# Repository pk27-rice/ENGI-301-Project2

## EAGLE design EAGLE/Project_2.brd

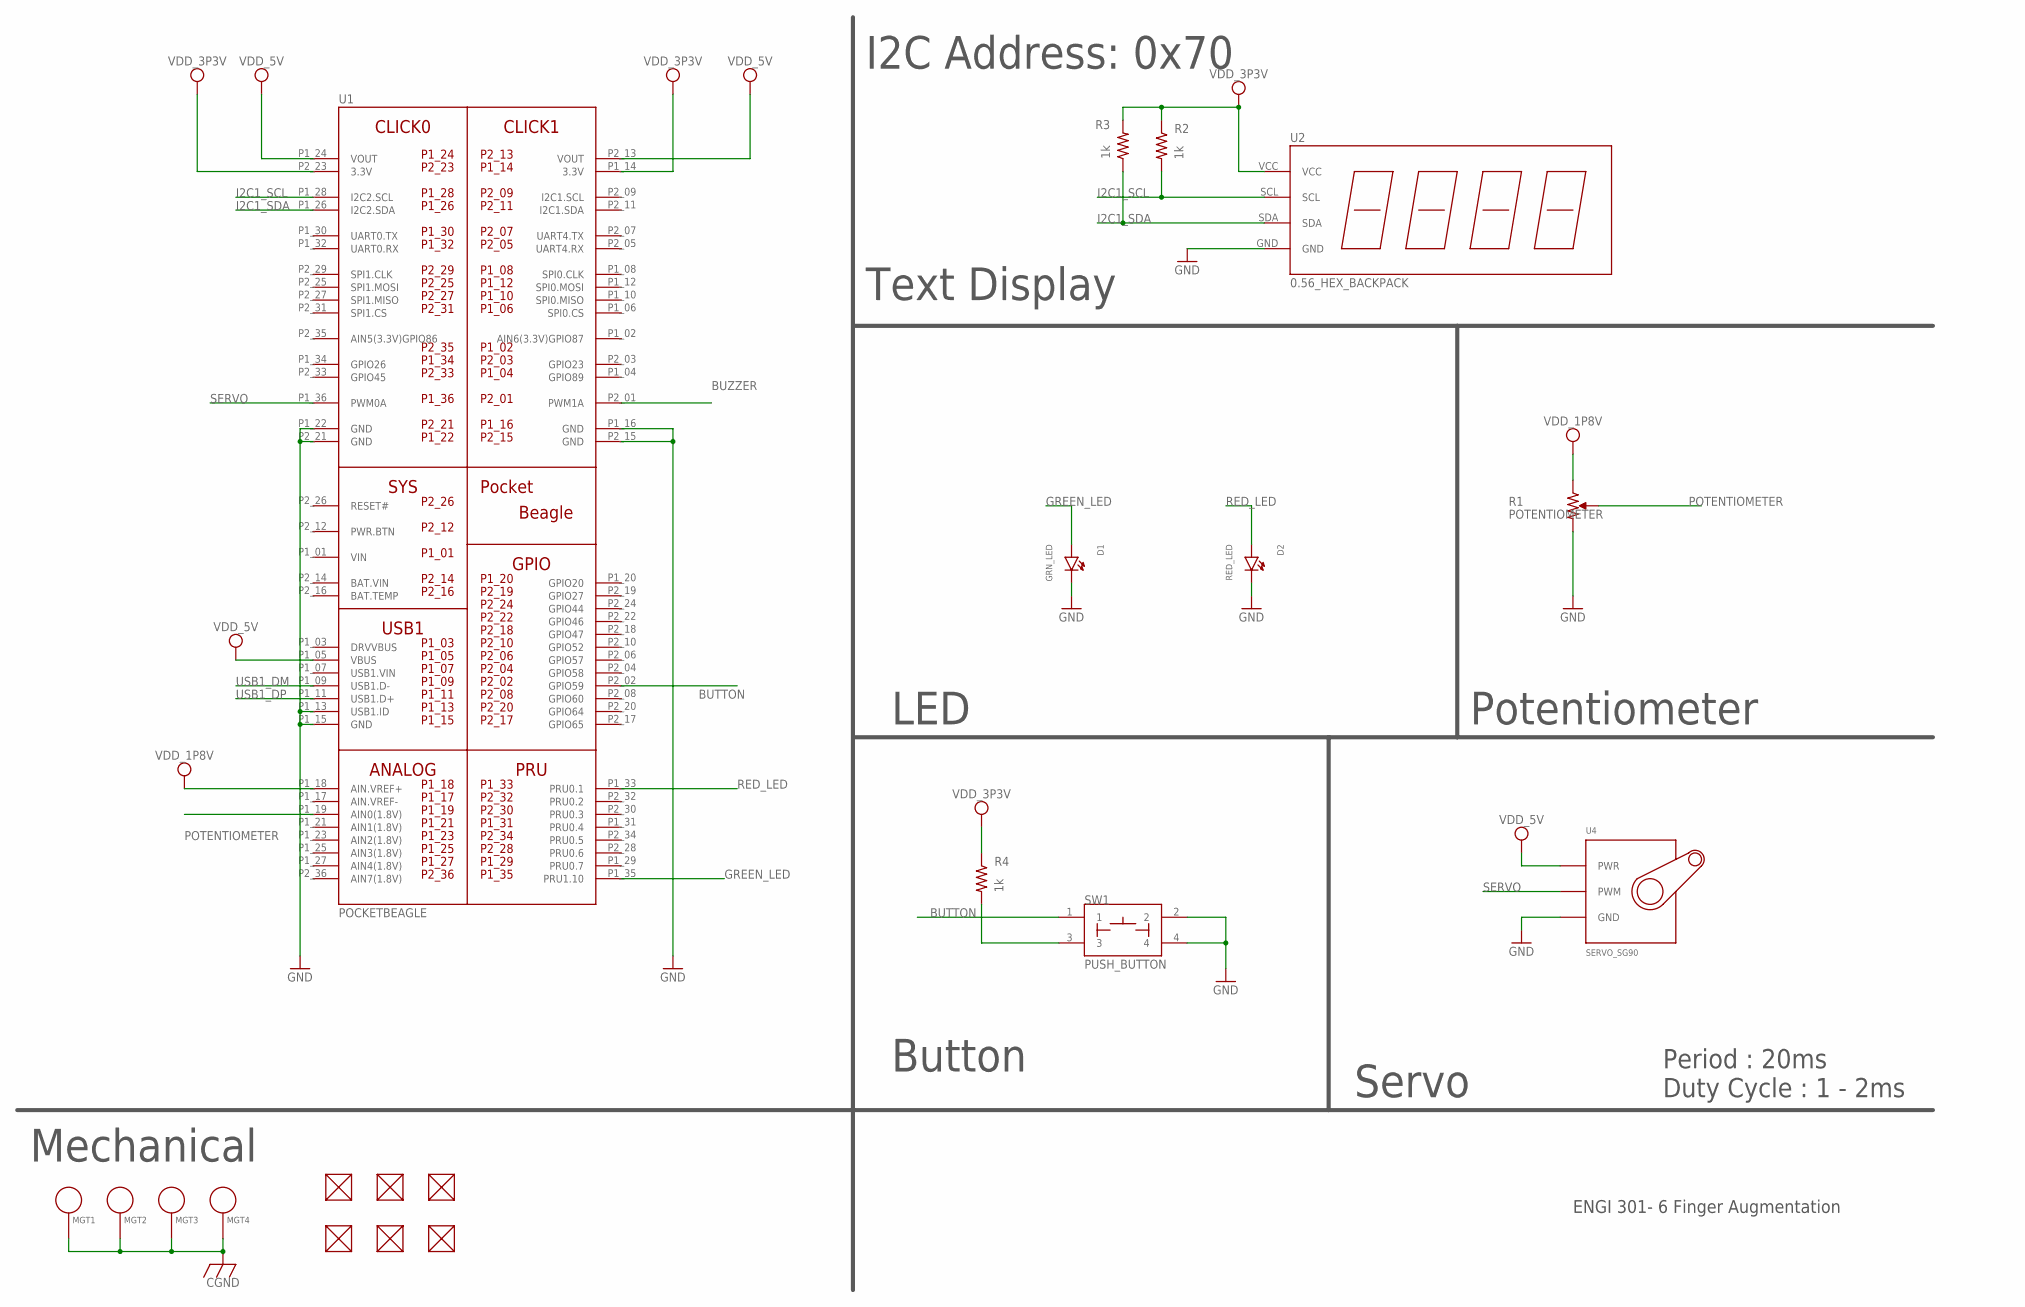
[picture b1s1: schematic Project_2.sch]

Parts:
D1: GRN_LED; EIA-STD
D2: RED_LED; EIA-STD
FUD1, FUD2, FUD3, FUD4, FUD5, FUD6: FIDUCIAL; FIDUCIAL_40MIL
MGT1, MGT2, MGT3, MGT4: MOUNTING_HOLE
R1: POTENTIOMETER; POT-PO90S
R2, R3, R4: 1k; R0603
SW1: PUSH_BUTTON; BUTTON_12.5MM
U1: POCKETBEAGLE
U2: 0.56_HEX_BACKPACK
U4: SERVO_SG90; SERVO-X1

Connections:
BAT.VIN: U1.P2_14 (BAT.VIN)
BUTTON: R4.2, SW1.1, SW1.3, U1.P2_02 (GPIO59)
BUZZER: U1.P2_01 (PWM1A)
CGND: MGT1.P$1, MGT2.P$1, MGT3.P$1, MGT4.P$1
GND: D1.CATHODE, D2.CATHODE, R1.CW, SW1.2, SW1.4, U1.P1_13 (USB1.ID), U1.P1_15 (GND), U1.P1_16 (GND), U1.P1_22 (GND), U1.P2_15 (GND), U1.P2_21 (GND), U2.GND, U4.GND
GREEN_LED: D1.ANODE, U1.P1_35 (PRU1.10)
I2C1_SCL: R2.2, U1.P1_28 (I2C2.SCL), U2.SCL
I2C1_SDA: R3.1, U1.P1_26 (I2C2.SDA), U2.SDA
POTENTIOMETER: R1.S, U1.P1_19 (AIN0(1.8V))
RED_LED: D2.ANODE, U1.P1_33 (PRU0.1)
SERVO: U1.P1_36 (PWM0A), U4.SIG (PWM)
USB1_DM: U1.P1_09 (USB1.D-)
USB1_DP: U1.P1_11 (USB1.D+)
VDD_1P8V: R1.CCW, U1.P1_18 (AIN.VREF+)
VDD_3P3V: R2.1, R3.2, R4.1, U1.P1_14 (3.3V), U1.P2_23 (3.3V), U2.VCC
VDD_5V: U1.P1_05 (VBUS), U1.P1_24 (VOUT), U1.P2_13 (VOUT), U4.PWR
VIN: U1.P1_01 (VIN)

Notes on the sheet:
Text Display
LED
Potentiometer
Button
Servo
I2C Address: 0x70
ENGI 301- 6 Finger Augmentation
Period : 20ms Duty Cycle : 1 - 2ms
Mechanical

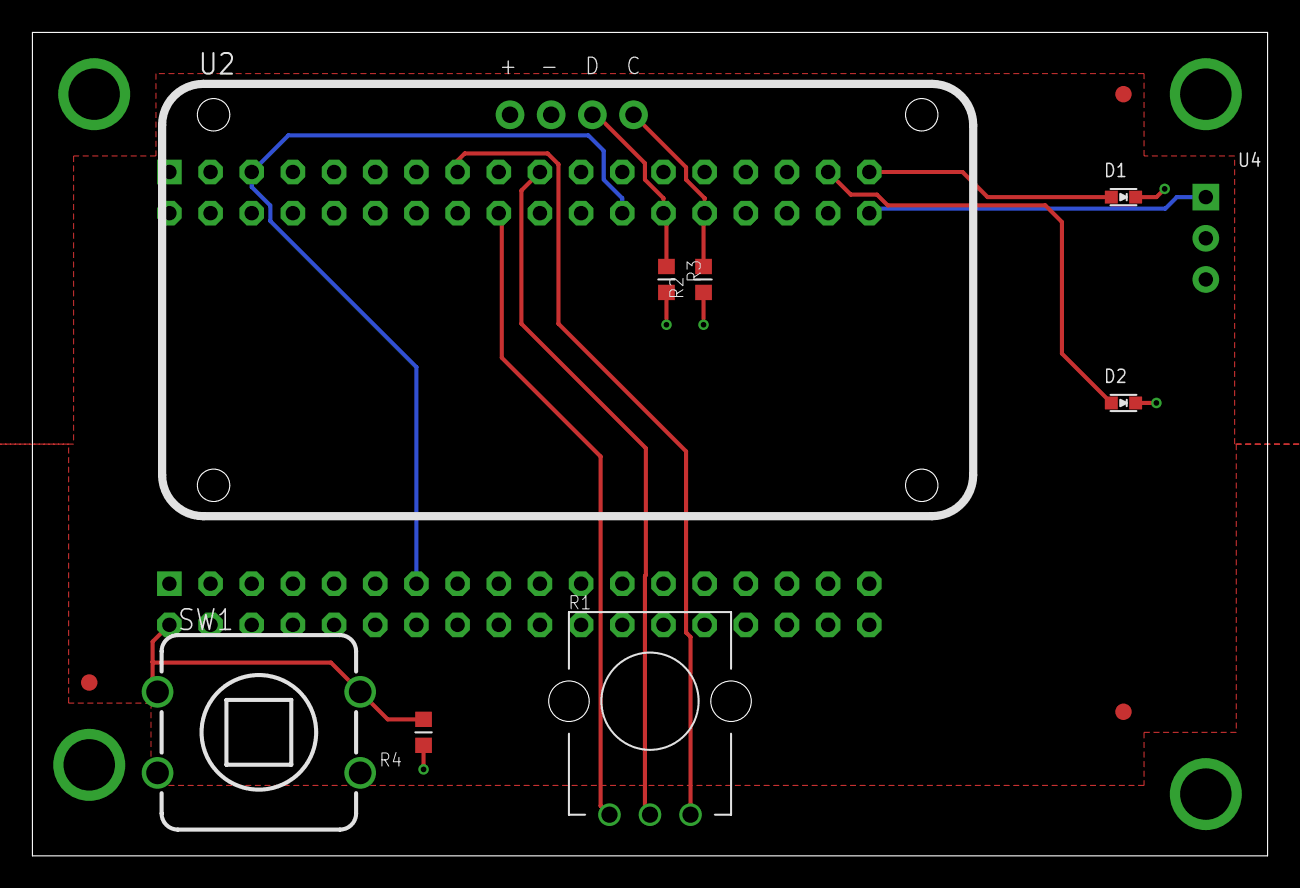
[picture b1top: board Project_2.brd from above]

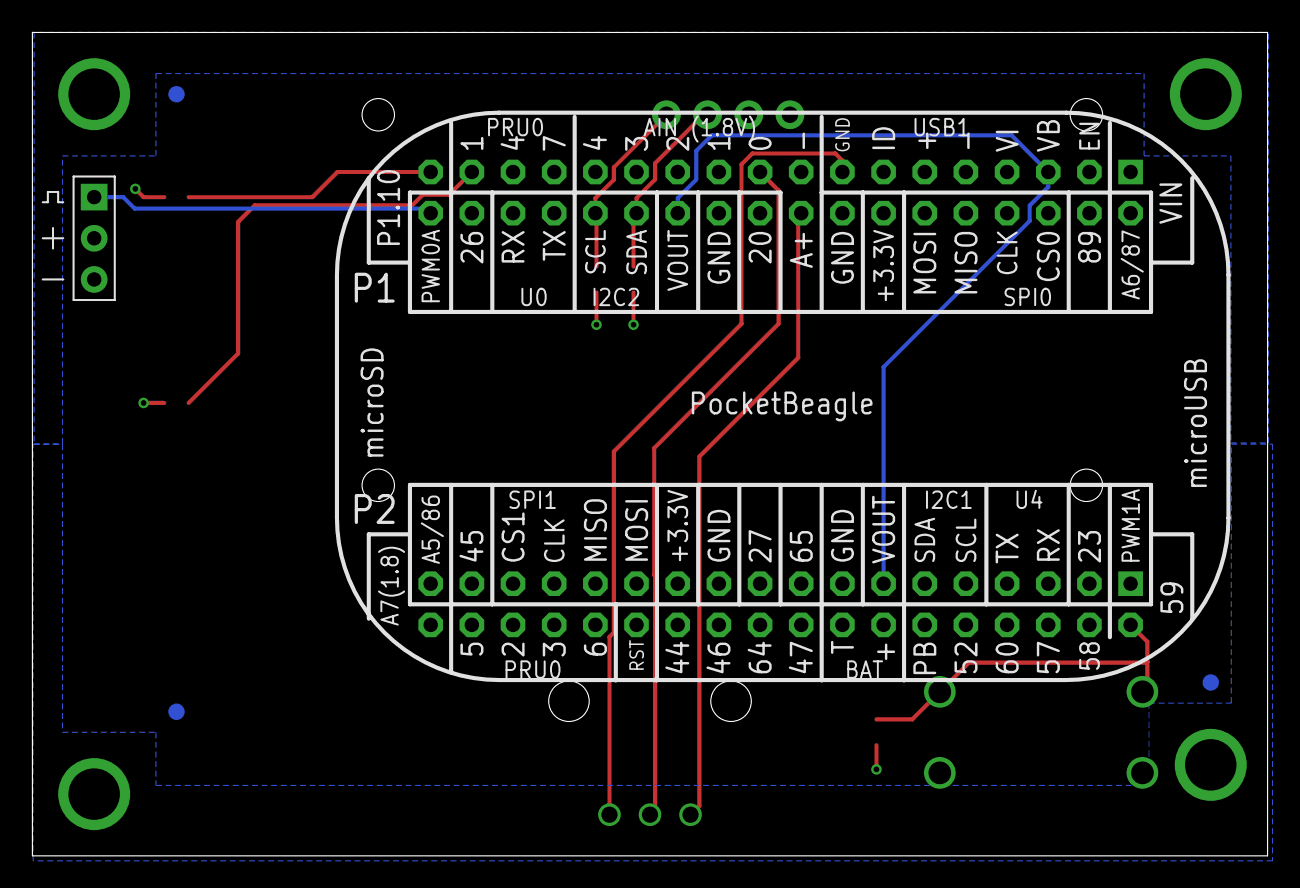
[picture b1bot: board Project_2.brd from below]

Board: 4 copper layers, 76.2 x 50.8 mm, 20 parts (5 on the bottom side), 12 nets.

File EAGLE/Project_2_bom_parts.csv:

"Part";"Value";"Device";"Package";"Description";"";
"D1";"GRN_LED";"LED";"EIA-STD";"EIA-STD LED, LTST-C191TBKT";"";
"D2";"RED_LED";"LED";"EIA-STD";"EIA-STD LED, LTST-C191TBKT";"";
"FUD1";"FIDUCIAL";"FIDUCIAL";"FIDUCIAL_40MIL";"";"";
"FUD2";"FIDUCIAL";"FIDUCIAL";"FIDUCIAL_40MIL";"";"";
"FUD3";"FIDUCIAL";"FIDUCIAL";"FIDUCIAL_40MIL";"";"";
"FUD4";"FIDUCIAL";"FIDUCIAL";"FIDUCIAL_40MIL";"";"";
"FUD5";"FIDUCIAL";"FIDUCIAL";"FIDUCIAL_40MIL";"";"";
"FUD6";"FIDUCIAL";"FIDUCIAL";"FIDUCIAL_40MIL";"";"";
"MGT1";"MOUNTING_HOLE";"MOUNTING_HOLE";"MOUNTING_HOLE";"Chassis Mounting Hole w/GND connection ability";"";
"MGT2";"MOUNTING_HOLE";"MOUNTING_HOLE";"MOUNTING_HOLE";"Chassis Mounting Hole w/GND connection ability";"";
"MGT3";"MOUNTING_HOLE";"MOUNTING_HOLE";"MOUNTING_HOLE";"Chassis Mounting Hole w/GND connection ability";"";
"MGT4";"MOUNTING_HOLE";"MOUNTING_HOLE";"MOUNTING_HOLE";"Chassis Mounting Hole w/GND connection ability";"";
"R1";"POTENTIOMETER";"POTENTIOMETER";"POT-PO90S";"Potentiometer - Examples:";"";
"R2";"1k";"R_R0603";"R0603";"RESISTOR, American symbol";"";
"R3";"1k";"R_R0603";"R0603";"RESISTOR, American symbol";"";
"R4";"1k";"R_R0603";"R0603";"RESISTOR, American symbol";"";
"SW1";"PUSH_BUTTON";"PUSH_BUTTON";"BUTTON_12.5MM";"";"";
"U1";"POCKETBEAGLE";"POCKETBEAGLE";"POCKETBEAGLE";"";"";
"U2";"0.56_HEX_BACKPACK";"0.56_HEX_BACKPACK";"0.56_HEX_BACKPACK";"0.56" LED HEX Backback - Adafruit HT16K33 -";"";
"U4";"SERVO_SG90";"SERVO_SG90";"SERVO-X1";"";"";

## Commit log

2022-12-05 Test
